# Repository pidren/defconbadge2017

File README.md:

# DEFCON 25 Custom Badge
Custom PCB design and code for DefCon 25 badge.
Credits to @mschuldt for help with the PCB design.

## Demo Video
[Link to Demo Video](https://www.youtube.com/watch?v=TrFcW3AFYnM)

## Why was this built?
For fun. Also I just wanted to learn how to do something I don't know how to do. At all.

## Designing the Custom PCB
Coming up with the final design took about 5 months of continuous redesigning and prototyping.
It also took a long time mostly because I didn't know anything about EE before this project. :)
The main goals of the PCB was that we would be able to fit all the components desired within
the smallest surface area possible, while also looking pleasant and something you'd want to
wear around your neck.

## What does it do?
- Each individual badge will connect to (unfortunately) hardcoded WiFi network.
- Once connected to a WiFi network, the badges will try to find their "sibling" badges by broadcasting itself on the network.
- A badge will never learn a sibling badge twice, but will try to find as many nearby siblings as possible.
- When a badge knows of at least one sibling in nearby viscinity it will start communicating.
- All badges will communicate to each other independently, and all badges will communicate to all other badges that is learned.

## Required Components for Assembly (per badge)
- Custom PCB printed by fab of your choice
  - For this badge, I used [Oshpark](https://oshpark.com/)
  - `vers2_cheaper.kicad_pcb` is the KiCAD file you can upload.
- [SSD1306 OLED Screen](https://www.amazon.com/gp/your-account/order-history?ie=UTF8&ref_=ya_d_c_yo&)
- [ESP8266 NodeMCU](https://www.amazon.com/gp/product/B010O1G1ES/ref=oh_aui_detailpage_o07_s00?ie=UTF8&psc=1)
- 220 Ohm resistors x 11
- RGB LED x 3
- 3mm LED x 2
- [3.7v 500mAh LiPo battery](https://www.adafruit.com/product/1578)
- Male microUSB connector, part only

## How to Assemble
- Basically solder on all the parts.
- Flash ESP with the arduino code using Arduino IDE version 1.6.4 and above
  - To compile correctly, you must have these libraries installed:
    - Adafruit_GFX_Library
    - Adafruit_SSD1306 Library 
    - Use board manager to install ESP modules. You'll be using the NodeMCU 1.0 ESP 12E board module.
  - You must flash in NodeMCU 1.0 ESP 12E mode. This mode has all the settings you need for the board so you should not have to touch anything.
- The battery does need manual assembly:
  - Clip off the JST end off of the LiPoly battery and solder onto the male microUSB part. 

## Useful Links
- [Pin mapping woes when addressing NodeMCU ESP GPIO pins in Arduino](https://github.com/esp8266/Arduino/issues/584)
- [If you accidentally "brick" your ESP and need to undo the damage](https://github.com/espressif/esptool/issues/213)
- [How to best work with SSD1306](http://arduino-er.blogspot.com/2016/04/nodemcu-esp8266-to-display-on-128x64.html)

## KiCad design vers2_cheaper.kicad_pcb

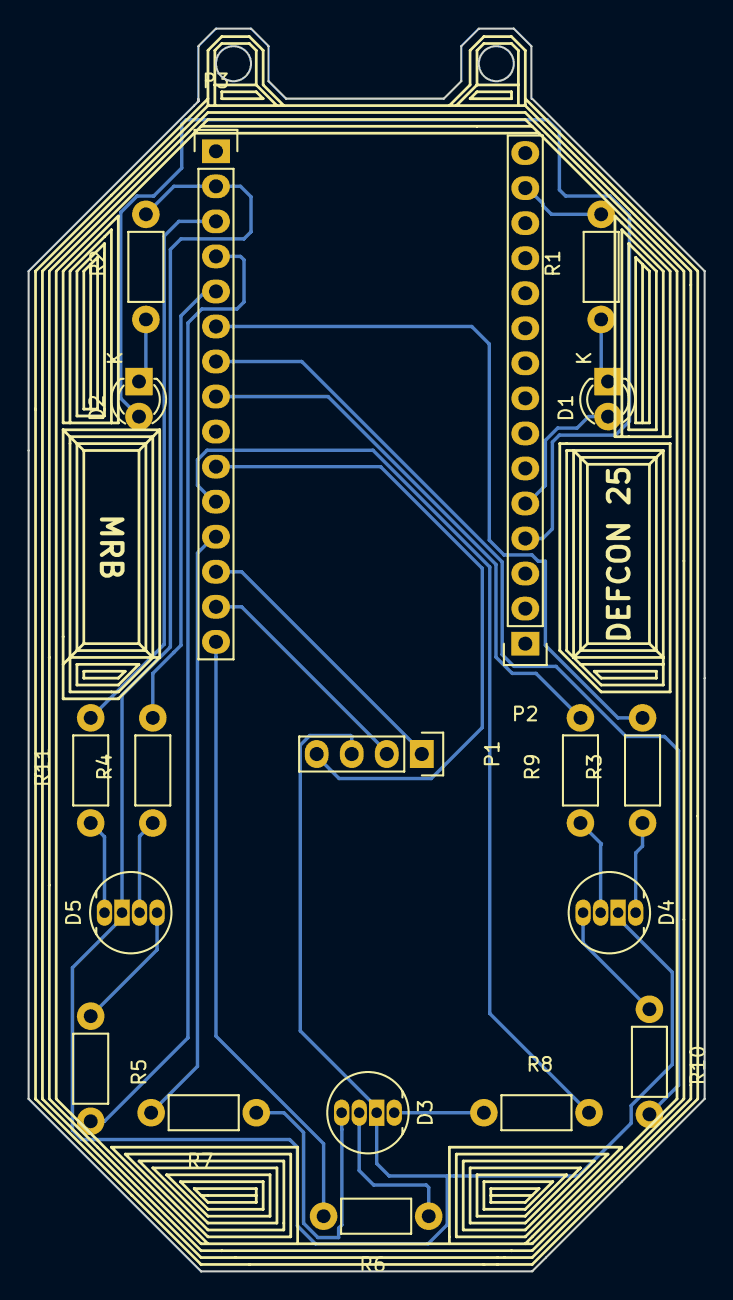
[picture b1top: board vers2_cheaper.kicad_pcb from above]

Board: 2 copper layers, 49.0 x 90.1 mm, 19 parts (0 on the bottom side), 28 nets.

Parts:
D1, D2: LED; LED-3MM
D3, D4, D5: LED_RCBG; LED-RGB-5MM_Common_Cathode
P1: CONN_01X4; Pin_Header_Straight_1x04
P2, P3: CONN_01X15; Pin_Header_Straight_1x15
R1, R2, R3, R4, R5, R6, R7, R8, R9, R10, R11: 10k; Resistor_Horizontal_RM7mm

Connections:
3_3v: P1.4, P3.10
GND_2: D3.2, D4.2, D5.2, P1.3, P3.2, R2.2
GND_14: P2.14, R1.2
unnamed: D1.1, R1.1
unnamed: D2.1, R2.1
unnamed: D3.1, R8.1
unnamed: D3.3, R6.1
unnamed: D3.4, R7.1
unnamed: D4.1, R3.1
unnamed: D4.3, R9.1
unnamed: D4.4, R10.1
unnamed: D5.1, R11.1
unnamed: D5.3, R4.1
unnamed: D5.4, R5.1
d0: P3.15, R6.2
d1: P1.2, P3.14
d2: P1.1, P3.13
d3: P3.12, R7.2
d4: P3.11, R8.2
d5: P3.8, R9.2
d6: P3.7, R10.2
d7: P3.6, R3.2
d8: P3.5, R4.2
rsv: P2.2, P2.3
rx: P3.4, R5.2
sd2: D1.2, P2.5
sd3: D2.2, P2.4
tx: P3.3, R11.2

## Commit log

2017-07-04 This is initial commit containing the correct ping mapping for all the RGBs and top LEDs.
2017-07-04 Adding README
2017-07-04 Cleaning out some test code
2017-07-04 Corrected pin mappings and setup a test
2017-07-12 Lots of library functions added 1. RGB color channel controls, rainbow function 2. LED controls, flicker 3. Starting loading/banner done 4. Wrote notes in sections where Wifi Server setup should go.
2017-07-12 README fixed
2017-07-16 Code clean up, server initialization done, need to work on client
2017-07-17 Cleaned up unnecessary code; changed HTTP server to UDP server; While connecting to WiFi LEDs flicker
2017-07-17 Completely hardcoded, but two badges can now talk to each other
2017-07-17 Cleanup
2017-07-19 More synchronization code
2017-07-20 Fixed the issue with addressing and addressing siblings
2017-07-24 stuff
2017-08-09 Updating README
2017-08-09 Correcting word vomit that happened on README
2017-08-10 Adding useful links to README
2017-08-10 Correcting broken links
2019-10-15 Create LICENSE
